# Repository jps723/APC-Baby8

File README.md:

# APCBaby8 Build Notes 2/16/20

This project is in partnership with [Bantam Tools](https://www.bantamtools.com)

**Design Notes:**

This design is based on the Atari Punk Console and the Baby8 Step Sequencer.  It utilizes three 555 timers, and a 4017 decade counter, to emit a square wave in a repeating series of frequencies.  It’s a stackable design broken into UI and Utility boards.

The design operates off of 9v, with ‘+/-‘ symbols etched into the top layer of the bottom board, indicating polarity. There are additional ‘–‘ etchings indicating the required ‘notch’ orientation for all of the ICs.  The arrows indicate the directions that the boards should be facing when stacked.

The UI board contains 11 variable resistors in total; 8 for defining the pitch to be played in the sequencer, and three others for controlling the rate at which the sequence advances, the pulse width of the oscillation, and the master volume.

Each of the 8 pitch variable resistors is connected to an output pin of a 4017 decade counter (located on the utility board), which counts through the 8 step sequence.  As each step is passed, the emitted voltage as determined by the position of the pot is applied to oscillator A of the APC, affecting its frequency.  Each step has an associated LED located above it for indicating which step is being played. The 1N4148 diode is for preventing noise from unintended steps.

The Utility board contains the decade counter, a 555 timer that serves as the master clock, and two more 555 timers serving as oscillators A and B for the APC.  Oscillator A is in astable mode, and oscillator B is in monostable mode, with its trigger coming from the output of oscillator A.  Oscillator B has a pot connected to it for varying the pulse width of the oscillation. The 4017 decade counter emits 10 steps, however step 9 triggers the reset pin, limiting the sequence to 8.  The output voltage from the stepped variable resistors are applied to the discharge pin on Oscillator B, dictating the charge rate of the attached capacitor, and ultimately the oscillation frequency.

## **Build Process:**

**Bottom Board:**
**Top Layer:**
Bits: 1/32” / 1/64”
Mill Time: ~4 ½mins

**Bottom Layer:**
Bits: 1/32” / 1/64”
Mill Time: ~14 ½mins

**Top Board:
Bottom Layer:**
Bits: 1/32” / 1/64”
Mill Time: ~17 ½mins

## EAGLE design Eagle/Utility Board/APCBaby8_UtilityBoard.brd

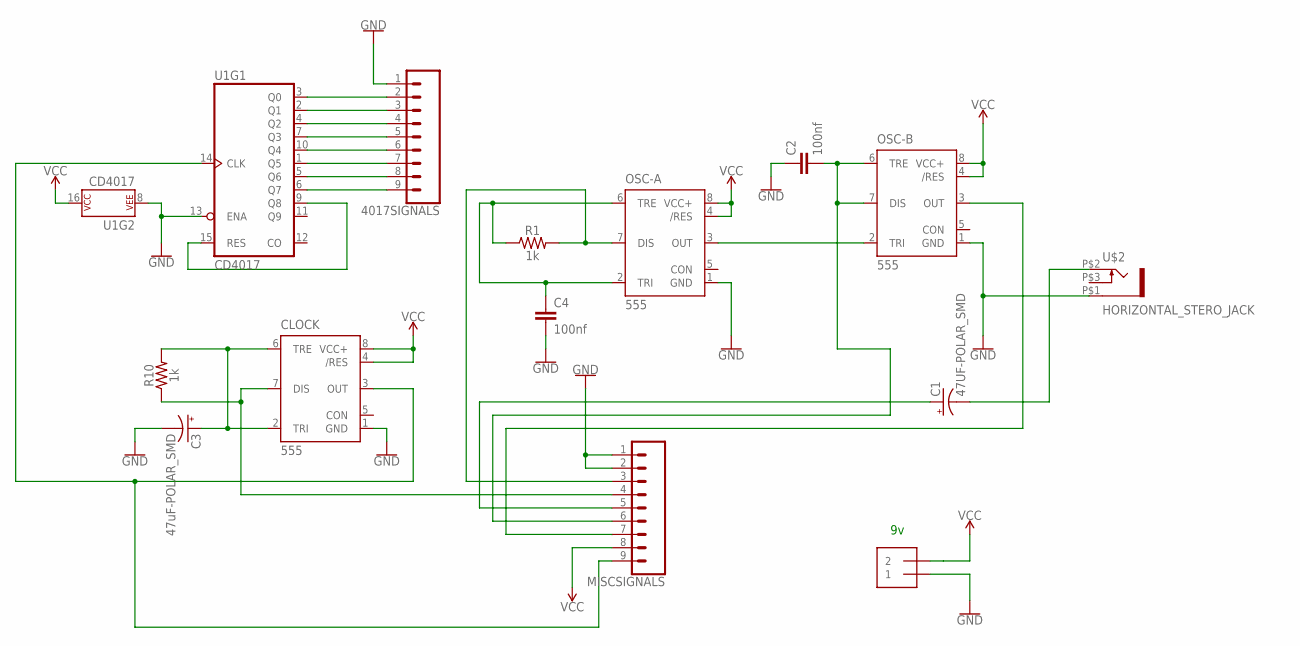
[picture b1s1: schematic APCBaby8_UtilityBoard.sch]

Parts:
9V: 9v; 1X2-3.5MM
4017SIGNALS: CONN_09LONGPADS; 1X09_LONGPADS
C1: 47UF-POLAR_SMD; PANASONIC_D
C2, C4: 100nf; 0805
C3: 47uF-POLAR_SMD; PANASONIC_D
CLOCK: 555; DIP08-KIT
MISCSIGNALS: CONN_09LONGPADS; 1X09_LONGPADS
OSC-A: 555; DIP08-KIT
OSC-B: 555; DIP08-KIT
R1, R10: 1k; 0805
U1: CD4017; DIP16
U$2: HORIZONTAL_STERO_JACK; HORIZONTAL_STEREO_JACK

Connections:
CLOCK: CLOCK.3 (OUT), MISCSIGNALS.9, U1.14 (CLK)
GND: 9V.1, 4017SIGNALS.1, C2.1, C3.-, C4.2, CLOCK.1 (GND), MISCSIGNALS.1, MISCSIGNALS.2, OSC-A.1 (GND), OSC-B.1 (GND), U1.8 (P$V-), U1.13 (ENA), U$2.P$1 (1)
unnamed: 4017SIGNALS.2, U1.3 (Q0)
unnamed: 4017SIGNALS.3, U1.2 (Q1)
unnamed: 4017SIGNALS.4, U1.4 (Q2)
unnamed: 4017SIGNALS.5, U1.7 (Q3)
unnamed: 4017SIGNALS.6, U1.10 (Q4)
unnamed: 4017SIGNALS.7, U1.1 (Q5)
unnamed: 4017SIGNALS.8, U1.5 (Q6)
unnamed: 4017SIGNALS.9, U1.6 (Q7)
unnamed: C1.-, U$2.P$2 (2)
unnamed: C3.+, CLOCK.2 (TRI), CLOCK.6 (TRE), R10.2
unnamed: C4.1, OSC-A.2 (TRI), OSC-A.6 (TRE), R1.1
unnamed: OSC-A.3 (OUT), OSC-B.2 (TRI)
OUT: MISCSIGNALS.7, OSC-B.3 (OUT)
PUSESIG: C2.2, MISCSIGNALS.6, OSC-B.6 (TRE), OSC-B.7 (DIS)
RESET: U1.9 (Q8), U1.15 (RES)
STEPSIG: MISCSIGNALS.3, OSC-A.7 (DIS), R1.2
TEMPOSIG: CLOCK.7 (DIS), MISCSIGNALS.4, R10.1
VCC: 9V.2, CLOCK.4 (/RES), CLOCK.8 (VCC+), MISCSIGNALS.8, OSC-A.4 (/RES), OSC-A.8 (VCC+), OSC-B.4 (/RES), OSC-B.8 (VCC+), U1.16 (P$V+)
VOLSIG: C1.+, MISCSIGNALS.5

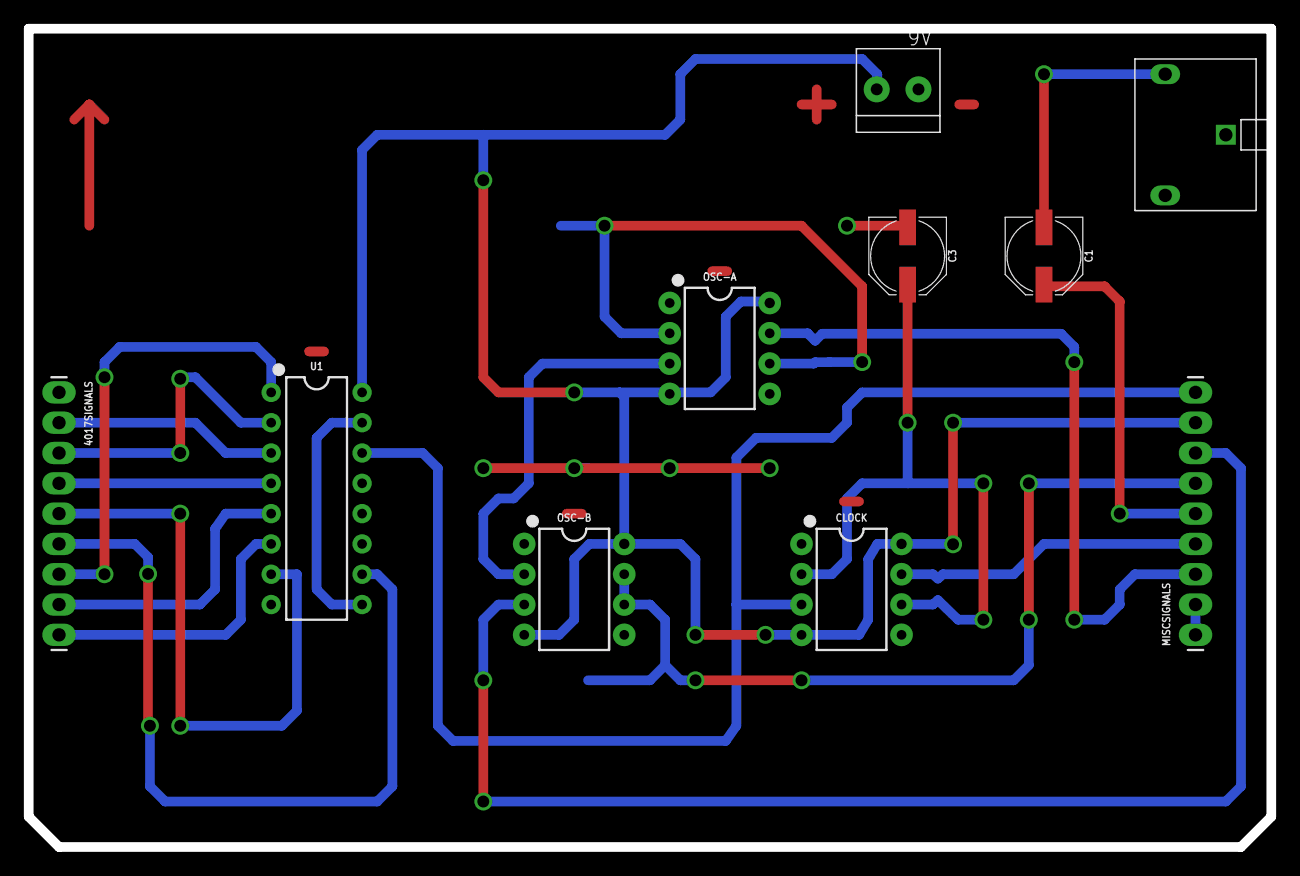
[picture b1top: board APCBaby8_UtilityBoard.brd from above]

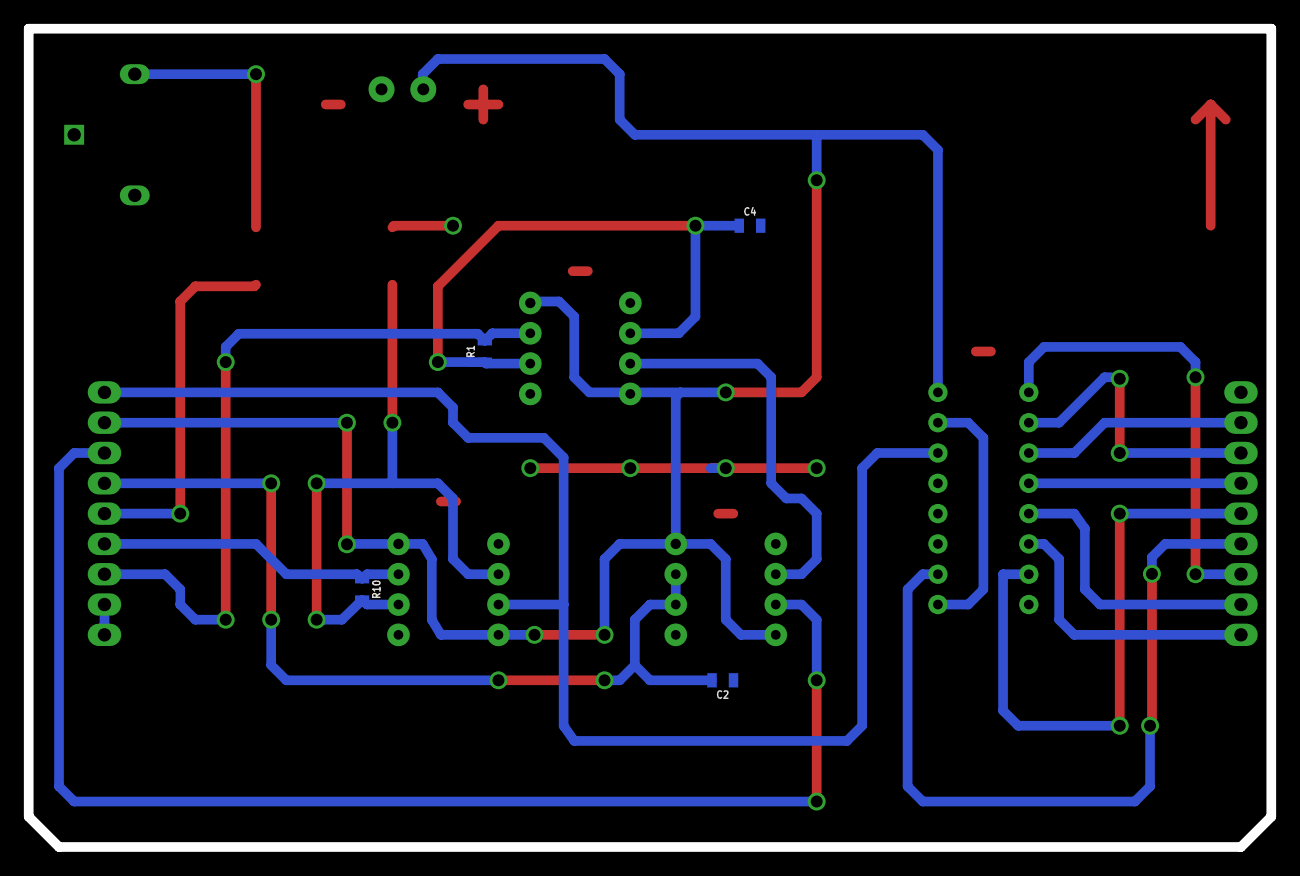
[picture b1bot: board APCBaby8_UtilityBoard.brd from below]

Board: 2 copper layers, 104.1 x 68.6 mm, 14 parts (4 on the bottom side), 21 nets.

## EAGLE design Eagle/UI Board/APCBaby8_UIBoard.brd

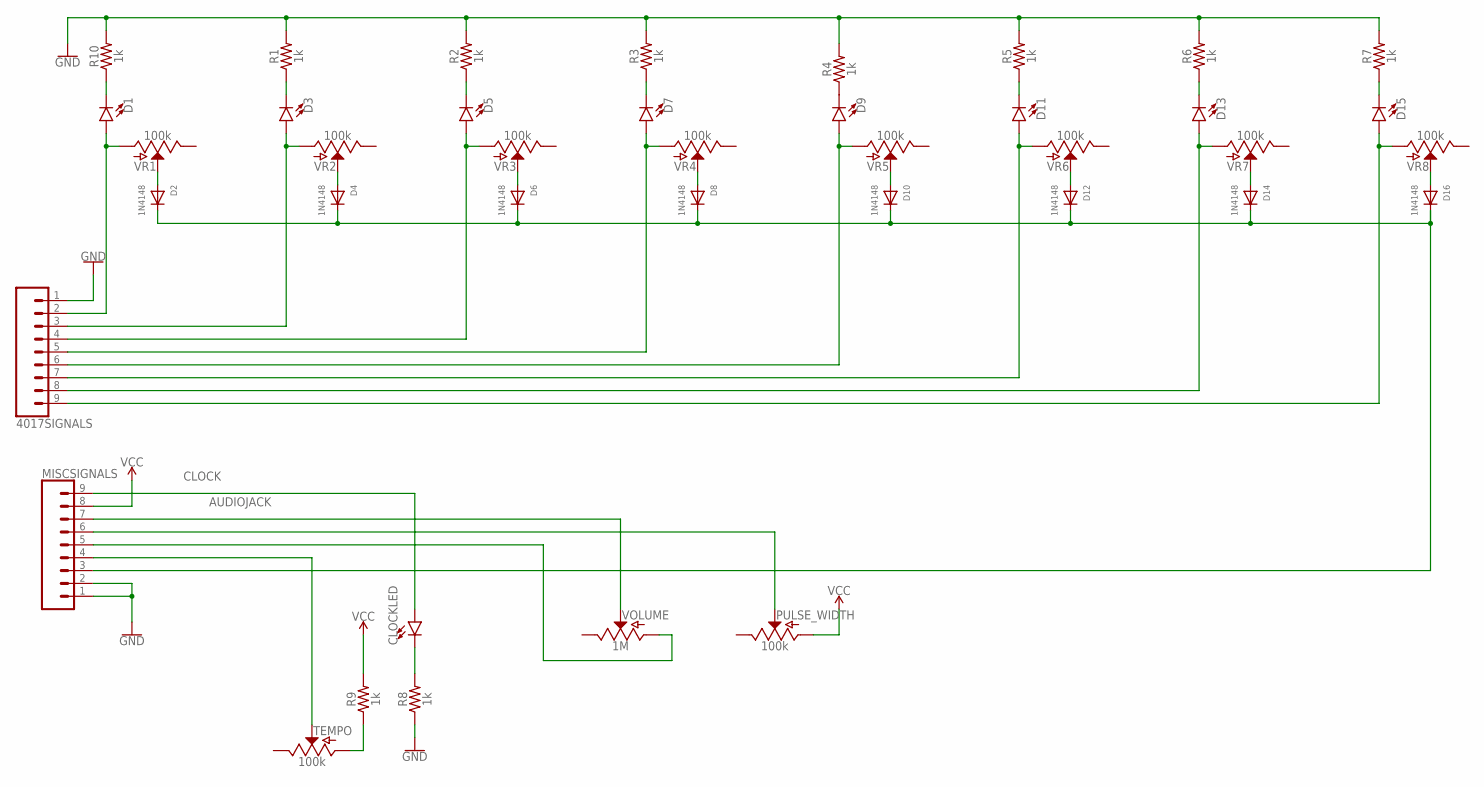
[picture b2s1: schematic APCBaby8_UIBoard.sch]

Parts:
4017SIGNALS: CONN_09LONGPADS; 1X09_LONGPADS
CLOCKLED: LED-3MM-NO_SILK; LED_3MM-NS
D1, D3, D5, D7, D9, D11, D13, D15: LED-3MM-NO_SILK; LED_3MM-NS
D2, D4, D6, D8, D10, D12, D14, D16: 1N4148; DO-1N4148
MISCSIGNALS: CONN_09LONGPADS; 1X09_LONGPADS
PULSE_WIDTH: 100k; POT-PTH-ALPS
R1, R2, R3, R4, R5, R6, R7, R8, R9, R10: 1k; 0805
TEMPO: 100k; POT-PTH-ALPS
VOLUME: 1M; POT-PTH-ALPS
VR1, VR2, VR3, VR4, VR5, VR6, VR7, VR8: 100k; POT-PTH-ALPS

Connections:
AUDIOJACK: MISCSIGNALS.7, VOLUME.P$2 (S)
CLOCK: CLOCKLED.A, MISCSIGNALS.9
GND: 4017SIGNALS.1, MISCSIGNALS.1, MISCSIGNALS.2, R1.2, R2.2, R3.2, R4.2, R5.2, R6.2, R7.2, R8.1, R10.2
unnamed: D9.K (C), R4.1
unnamed: D2.A, VR1.P$2 (S)
unnamed: D1.K (C), R10.1
unnamed: D4.A, VR2.P$2 (S)
unnamed: D3.K (C), R1.1
unnamed: R9.1, TEMPO.P$3 (A)
unnamed: D6.A, VR3.P$2 (S)
unnamed: D5.K (C), R2.1
unnamed: D8.A, VR4.P$2 (S)
unnamed: D7.K (C), R3.1
unnamed: D10.A, VR5.P$2 (S)
unnamed: D12.A, VR6.P$2 (S)
unnamed: D11.K (C), R5.1
unnamed: D14.A, VR7.P$2 (S)
unnamed: D13.K (C), R6.1
unnamed: D16.A, VR8.P$2 (S)
unnamed: D15.K (C), R7.1
unnamed: CLOCKLED.K (C), R8.2
PULSESIG: MISCSIGNALS.6, PULSE_WIDTH.P$2 (S)
STEP1: 4017SIGNALS.2, D1.A, VR1.P$3 (A)
STEP2: 4017SIGNALS.3, D3.A, VR2.P$3 (A)
STEP3: 4017SIGNALS.4, D5.A, VR3.P$3 (A)
STEP4: 4017SIGNALS.5, D7.A, VR4.P$3 (A)
STEP5: 4017SIGNALS.6, D9.A, VR5.P$3 (A)
STEP6: 4017SIGNALS.7, D11.A, VR6.P$3 (A)
STEP7: 4017SIGNALS.8, D13.A, VR7.P$3 (A)
STEP8: 4017SIGNALS.9, D15.A, VR8.P$3 (A)
STEPDIODES: D2.C, D4.C, D6.C, D8.C, D10.C, D12.C, D14.C, D16.C, MISCSIGNALS.3
TEMPOSIG: MISCSIGNALS.4, TEMPO.P$2 (S)
VCC: MISCSIGNALS.8, PULSE_WIDTH.P$3 (A), R9.2
VOLSIG: MISCSIGNALS.5, VOLUME.P$3 (A)

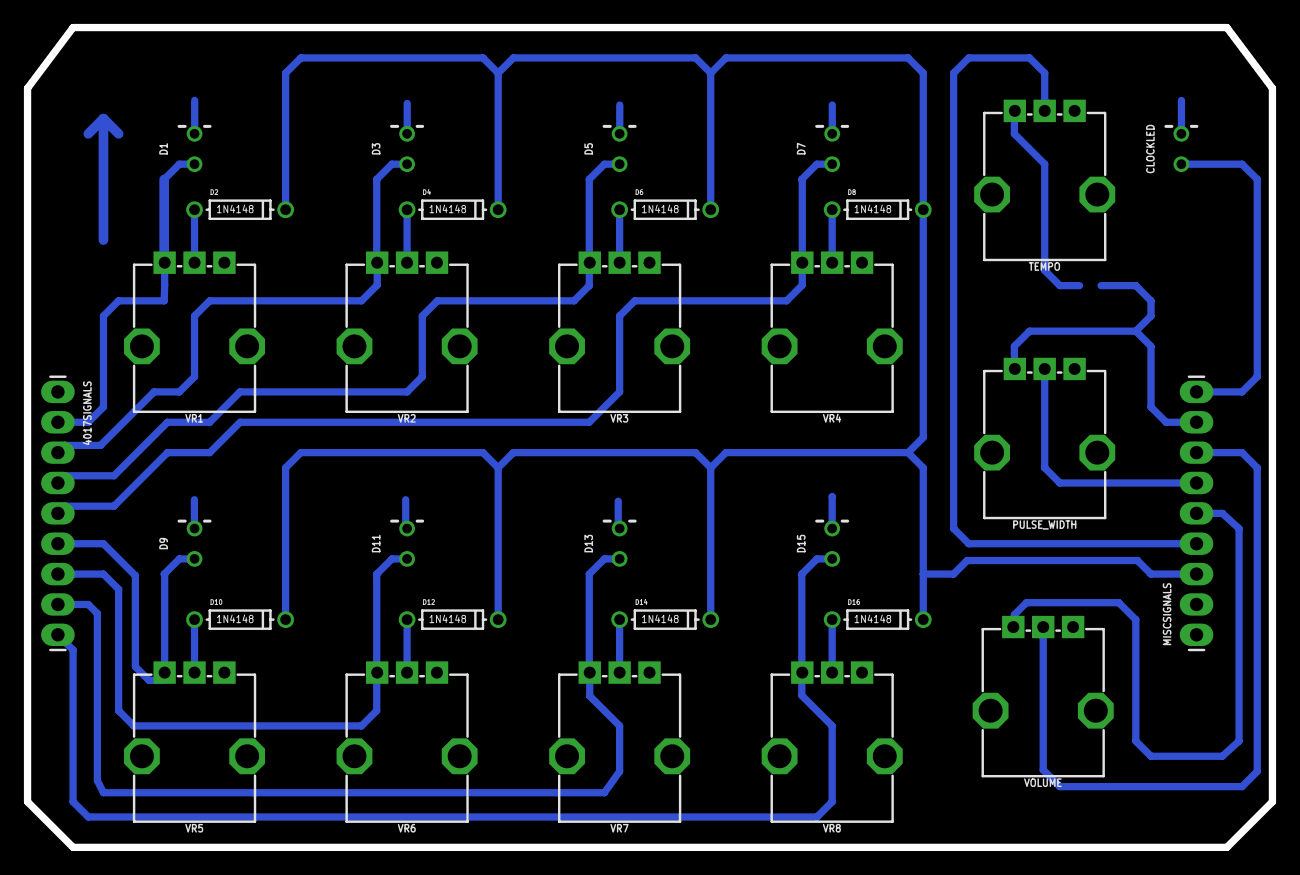
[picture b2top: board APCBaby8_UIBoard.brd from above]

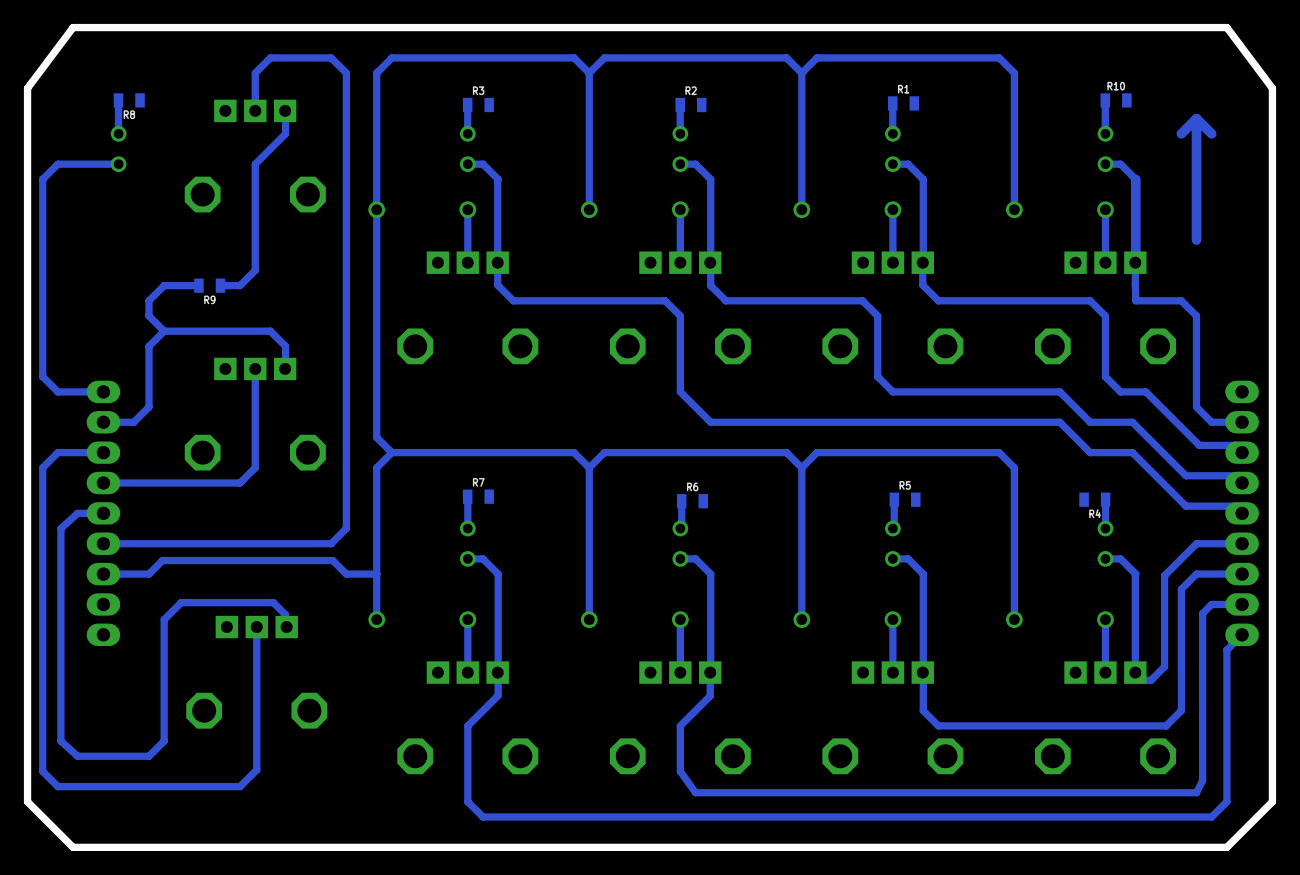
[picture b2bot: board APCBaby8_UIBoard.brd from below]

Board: 2 copper layers, 104.1 x 68.6 mm, 40 parts (10 on the bottom side), 34 nets.

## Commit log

2020-10-29 updated image path
2020-10-29 updated image path correctly
2020-10-30 added bantam tools credit

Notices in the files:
parts and their libraries:
SparkFun-LED: Licensing: Creative Commons ShareAlike 4.0 International - https://creativecommons.org/licenses/by-sa/4.0
